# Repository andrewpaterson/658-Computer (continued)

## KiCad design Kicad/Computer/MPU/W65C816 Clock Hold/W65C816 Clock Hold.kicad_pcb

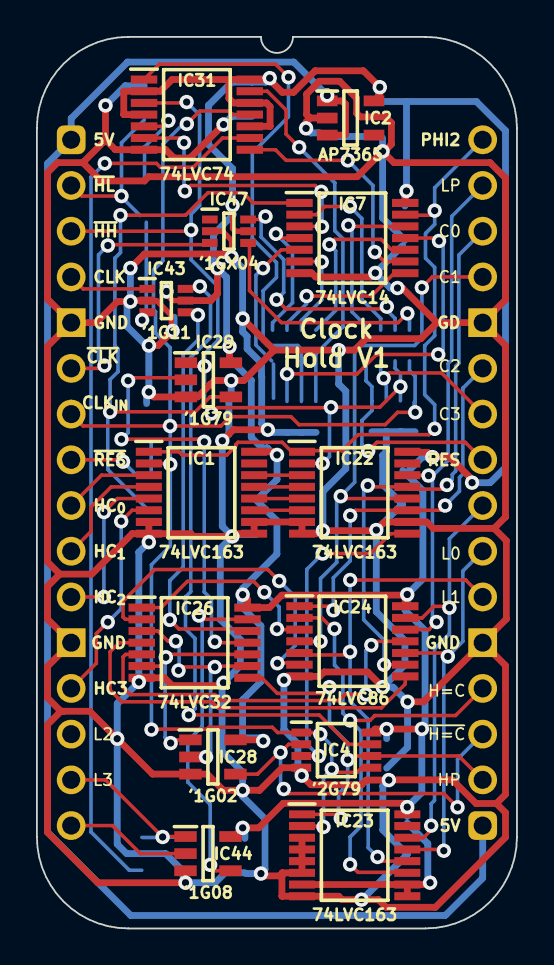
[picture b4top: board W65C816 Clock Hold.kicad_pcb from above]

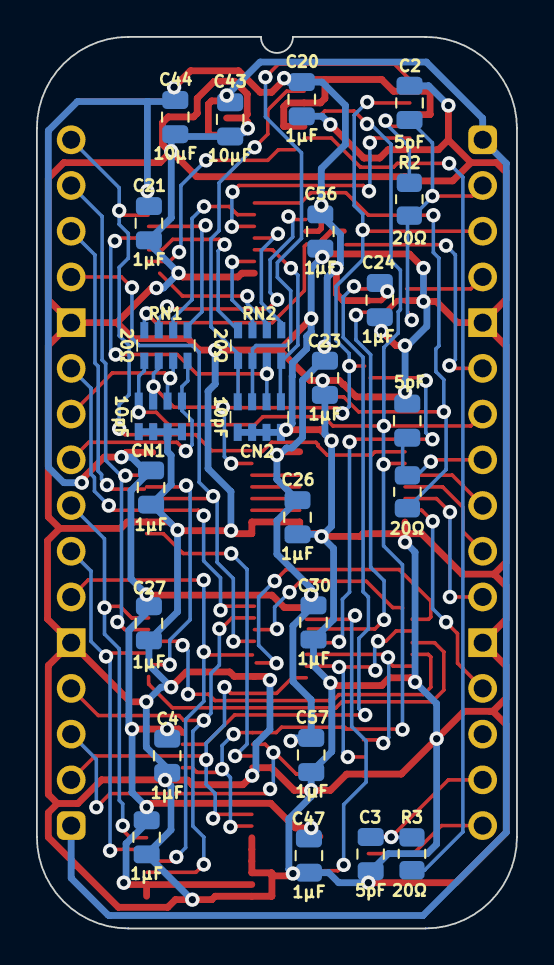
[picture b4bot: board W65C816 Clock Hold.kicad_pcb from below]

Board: 2 copper layers, 26.7 x 49.5 mm, 42 parts (27 on the bottom side), 60 nets.

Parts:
C1, C2, C3: 5pF; C_0805
C4, C20, C21, C23, C24, C25, C26, C27, C28, C30, C47, C56, C57: 1μF; C_0805
C43, C44: 10μF; C_0805
CN1, CN2: CA0612KRX7R9BB100
IC1, IC22, IC23: 74LVC163PW,118; SOP65P640X110-16N
IC2: AP7365-33WG-7; SOT95P285X130-5N
IC4: SN74LVC2G79DCTR; SOP65P400X130-8N
IC7: SN74LVC14APWRG4; SOP65P640X110-14N
IC24: SN74LVC86APWR; SOP65P640X120-14N
IC26: 74LVC32APW,118; SOP65P640X110-14N
IC28: 74LVC1G02GV,125; SOT95P275X110-5N
IC29: 74LVC1G79GV,125; SOT95P275X110-5N
IC31: 74LVC74APW,118; SOP65P640X110-14N
IC43: 74LVC1G11GW-Q100H; SOP65P210X110-6N
IC44: 74LVC1G08GV,125; SOT95P275X110-5N
IC47: 74LVC1GX04GW,125; SOP65P210X110-6N
J1: Conn_02x16_Counter_Clockwise; DIP-32_Board_W22.86mm
J2, J3: Pin_Header_01x16; PinHeader_1x16_P2.54mm_Vertical
R1, R2, R3: 20Ω; R_0805
RN1, RN2: CAY16-200J4LF; CAY16-F4

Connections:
5V: C43.1, IC2.1 (6VIn), IC2.3 (EN), J1.1, J1.17
/3.3V: C4.2, C20.1, C21.1, C23.1, C24.1, C25.1, C26.1, C27.1, C28.1, C30.1, C44.1, C47.1, C56.1, C57.1, IC1.16 (3V), IC2.5 (3.3VOut), IC4.8 (3V), IC7.14 (3V), IC22.16 (3V), IC23.7 (CEP), IC23.9 (~PE), IC23.10 (CET), IC23.16 (3V), IC24.14 (3V), IC26.14 (3V), IC28.5 (3V), IC29.5 (3V), IC31.2 (1D), IC31.4 (~1SD), IC31.10 (~2SD), IC31.12 (2D), IC31.14 (3V), IC43.5 (3V), IC44.5 (3V), IC47.5 (3V)
/CLK H.P.: IC7.4 (2Y), RN2.1 (R1)
/CLK H.P._{s}: CN2.1, IC7.5 (3A), RN2.8 (R1)
/CLK High Pulse_{f}: IC31.5 (1Q), R2.2
/CLK L.P.: IC7.8 (4Y), RN2.2 (R2)
/CLK L.P._{s}: CN2.2, IC7.11 (5A), RN2.7 (R2)
/CLK Low Pulse_{f}: IC31.9 (2Q), R3.2
/HC=CC _{CLK}: IC4.7 (1Q), IC43.6 (C)
/High Pulse+Low Pulse: IC26.11 (4Y), IC29.2 (CP)
/Hold Count_{0}: IC1.14 (Q0), IC22.3 (D0)
/Hold Count_{1}: IC1.13 (Q1), IC22.4 (D1)
/Hold Count_{2}: IC1.12 (Q2), IC22.5 (D2)
/Hold Count_{3}: IC1.11 (Q3), IC22.6 (D3)
/PHI2_{f}: IC7.1 (1A), IC29.4 (Q), R1.2
/~CLK High Pulse: IC7.3 (2A), IC31.6 (~1Q)
/~CLK High Reset Pulse: IC7.6 (3Y), RN2.3 (R3)
/~CLK High Reset Pulse_{s}: CN2.3, IC31.1 (~1RD), RN2.6 (R3)
/~CLK Low Pulse: IC7.9 (4A), IC31.8 (~2Q)
/~CLK Low Reset Pulse: IC7.10 (5Y), RN2.4 (R4)
/~CLK Low Reset Pulse_{s}: CN2.4, IC31.13 (~2RD), RN2.5 (R4)
/~HC=CC _{CLK}: IC4.3 (2Q), IC22.9 (~PE)
/~HC_{0=CC_{0}}: IC24.11 (4Y), IC26.5 (2B)
/~HC_{1=CC_{1}}: IC24.8 (3Y), IC26.4 (2A)
/~HC_{2=CC_{2}}: IC24.6 (2Y), IC26.2 (1B)
/~HC_{3=CC_{3}}: IC24.3 (1Y), IC26.1 (1A)
/~HC_{H=CC_{H}}: IC26.3 (1Y), IC26.9 (3A), IC28.2 (A)
/~HC_{L=CC_{L}}: IC26.6 (2Y), IC26.10 (3B), IC28.1 (B)
/~Hold High·CLK High Pulse·HC=CC: IC26.12 (4A), IC43.4 (Y)
/~Hold Low·CLK Low Pulse: IC26.13 (4B), IC44.4 (Y)
CLK: CN1.3, IC22.2 (CP), IC29.1 (D), IC31.3 (1CP), J1.3, RN1.6 (R3)
CLK High Pulse: C2.1, IC43.3 (B), J1.2, R2.1
CLK Low Pulse: C3.1, IC44.1 (B), J1.15, R3.1
CLK_{IN}: IC47.3 (X1), J1.6
Clk Count_{0}: IC23.14 (Q0), IC24.13 (4B), J1.24
Clk Count_{1}: IC23.13 (Q1), IC24.10 (3B), J1.23
Clk Count_{2}: IC23.12 (Q2), IC24.5 (2B), J1.22
Clk Count_{3}: IC23.11 (Q3), IC24.2 (1B), J1.20
GND: C1.2, C2.2, C3.2, C4.1, C20.2, C21.2, C23.2, C24.2, C25.2, C26.2, C27.2, C28.2, C30.2, C43.2, C44.2, C47.2, C56.2, C57.2, CN1.5, CN1.6, CN1.7, CN1.8, CN2.5, CN2.6, CN2.7, CN2.8, IC1.7 (CEP), IC1.8 (GND), IC1.9 (~PE), IC1.10 (CET), IC2.2 (GND), IC4.4 (GND), IC7.7 (GND), IC22.7 (CEP), IC22.8 (GND), IC22.10 (CET), IC23.3 (D0), IC23.4 (D1), IC23.5 (D2), IC23.6 (D3), IC23.8 (GND), IC24.7 (GND), IC26.7 (GND), IC28.3 (GND), IC29.3 (GND), IC31.7 (GND), IC43.2 (GND), IC44.3 (GND), IC47.2 (GND), J1.5, J1.12, J1.21, J1.28
HC Latch_{0}: IC22.14 (Q0), IC24.12 (4A), J1.31
HC Latch_{1}: IC22.13 (Q1), IC24.9 (3A), J1.30
HC Latch_{2}: IC22.12 (Q2), IC24.4 (2A), J1.29
HC Latch_{3}: IC22.11 (Q3), IC24.1 (1A), J1.27
HC=CC _{~CLK}: IC4.2 (1D), IC28.4 (Y), J1.19
Hold Count_{0}D: IC1.3 (D0), J1.9
Hold Count_{1}D: IC1.4 (D1), J1.10
Hold Count_{2}D: IC1.5 (D2), J1.11
Hold Count_{3}D: IC1.6 (D3), J1.13
unnamed: IC7.2 (1Y), RN1.2 (R2)
unnamed: IC7.12 (6Y), RN1.1 (R1)
unnamed: IC47.6 (Y), RN1.3 (R3)
unnamed: IC47.4 (~Y), RN1.4 (R4)
PHI2: C1.1, J1.8, R1.1
Reset: CN1.1, J1.25, RN1.8 (R1)
~CLK: CN1.4, IC1.2 (CP), IC4.1 (1CP), IC4.5 (2CP), IC23.2 (CP), IC31.11 (2CP), J1.7, RN1.5 (R4)
~HC=CC _{~CLK}: IC4.6 (2D), IC23.1 (~MR), IC26.8 (3Y), J1.18
~Hold High: IC43.1 (A), J1.4
~Hold Low: IC44.2 (A), J1.16
~PHI2: CN1.2, J1.26, RN1.7 (R2)
~Reset: IC1.1 (~MR), IC7.13 (6A), IC22.1 (~MR), J1.32

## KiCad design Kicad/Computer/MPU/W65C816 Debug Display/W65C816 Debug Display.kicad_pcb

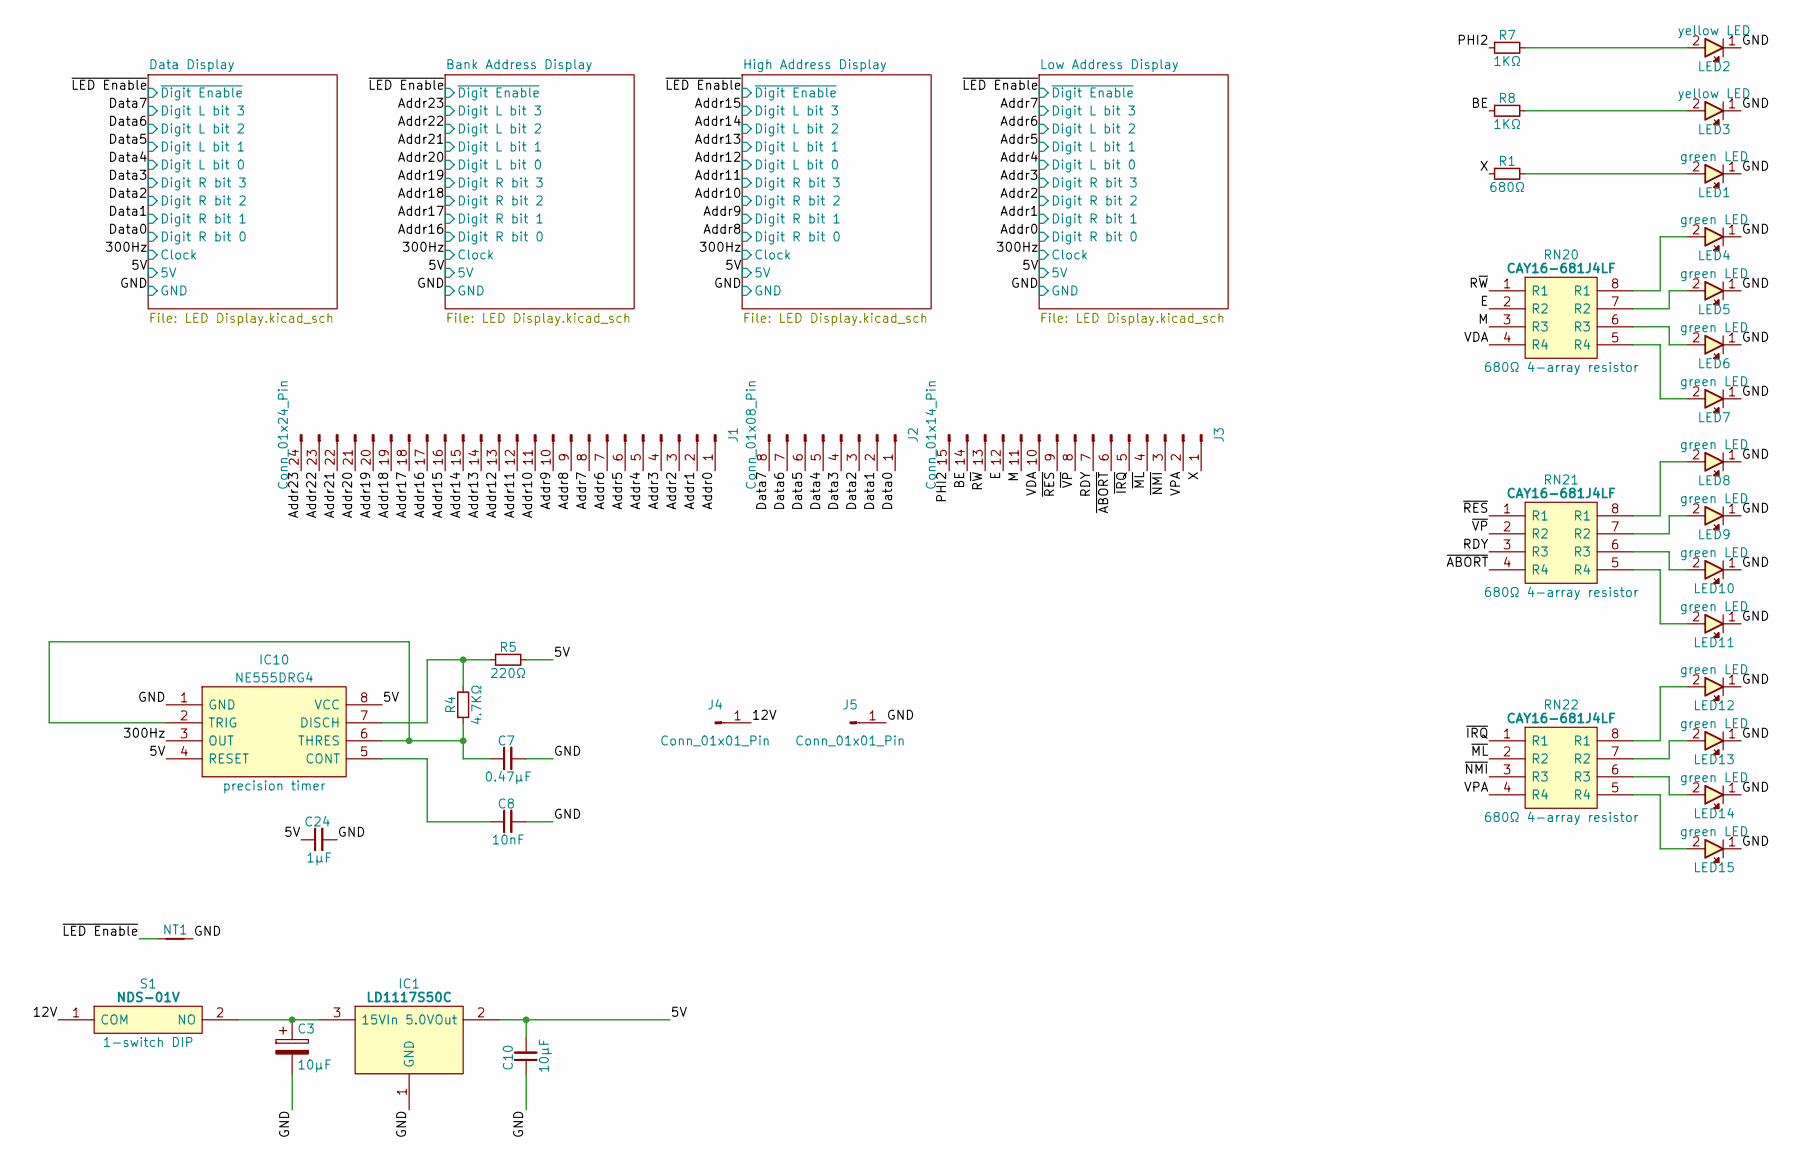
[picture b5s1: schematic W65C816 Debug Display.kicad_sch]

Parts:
C3: 10μF; CP_Radial_D4.0mm_P2.00mm
C7: 0.47μF; C_0805
C8: 10nF; C_0805
C10: 10µF; C_0805
C24: 1µF; C_0805
IC1: LD1117S50C; LD1117S33C; Manufacturer_Part_Number LD1117S50C
IC10: NE555DRG4; SOIC127P600X175-8N; Mouser Part Number 595-NE555DRG4
J1: Conn_01x24_Pin; PinHeader_1x24_P2.54mm_Vertical
J2: Conn_01x08_Pin; PinHeader_1x08_P2.54mm_Vertical
J3: Conn_01x14_Pin; PinHeader_1x15_P2.54mm_Vertical
J4, J5: Conn_01x01_Pin; PinHeader_1x01_P2.54mm_Vertical
LED1, LED4, LED5, LED6, LED7, LED8, LED9, LED10, LED11, LED12, LED13, LED14, LED15: 150224VS73100A; Manufacturer_Part_Number 150224VS73100A; Mouser Part Number 710-150224VS73100A
LED2, LED3: 150224YS73100A; 150224BS73100A
NT1: NetTie; NetTie-2_SMD_Pad0.5mm
R1: 680Ω; R_0805
R4: 4.7KΩ; R_0805
R5: 220Ω; R_0805
R7, R8: 1KΩ; R_0805
RN20, RN21, RN22: CAY16-681J4LF; CAY16-J4; Manufacturer_Part_Number CAY16-681J4LF; Mouser Part Number 652-CAY16-681J4LF
S1: NDS-01V; NDS01V; Mouser Part Number 113-NDS01V

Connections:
/5V: C24.1, IC1.2 (5.0VOut), IC10.4 (RESET), IC10.8 (VCC), R5.2; also elsewhere on the board
/12V: J4.1, S1.1 (COM)
/300Hz: IC10.3 (OUT); also elsewhere on the board
/Addr0: J1.1; also elsewhere on the board
/Addr1: J1.2; also elsewhere on the board
/Addr2: J1.3; also elsewhere on the board
/Addr3: J1.4; also elsewhere on the board
/Addr4: J1.5; also elsewhere on the board
/Addr5: J1.6; also elsewhere on the board
/Addr6: J1.7; also elsewhere on the board
/Addr7: J1.8; also elsewhere on the board
/Addr8: J1.9; also elsewhere on the board
/Addr9: J1.10; also elsewhere on the board
/Addr10: J1.11; also elsewhere on the board
/Addr11: J1.12; also elsewhere on the board
/Addr12: J1.13; also elsewhere on the board
/Addr13: J1.14; also elsewhere on the board
/Addr14: J1.15; also elsewhere on the board
/Addr15: J1.16; also elsewhere on the board
/Addr16: J1.17; also elsewhere on the board
/Addr17: J1.18; also elsewhere on the board
/Addr18: J1.19; also elsewhere on the board
/Addr19: J1.20; also elsewhere on the board
/Addr20: J1.21; also elsewhere on the board
/Addr21: J1.22; also elsewhere on the board
/Addr22: J1.23; also elsewhere on the board
/Addr23: J1.24; also elsewhere on the board
/BE: J3.14, R8.1
/Data0: J2.1; also elsewhere on the board
/Data1: J2.2; also elsewhere on the board
/Data2: J2.3; also elsewhere on the board
/Data3: J2.4; also elsewhere on the board
/Data4: J2.5; also elsewhere on the board
/Data5: J2.6; also elsewhere on the board
/Data6: J2.7; also elsewhere on the board
/Data7: J2.8; also elsewhere on the board
/E: J3.12, RN20.2 (R2)
/GND: C3.2, C7.2, C8.2, C24.2, IC1.1 (GND), IC10.1 (GND), J5.1, LED1.1, LED2.1, LED3.1, LED4.1, LED5.1, LED6.1, LED7.1, LED8.1, LED9.1, LED10.1, LED11.1, LED12.1, LED13.1, LED14.1, LED15.1, NT1.2; also elsewhere on the board
/M: J3.11, RN20.3 (R3)
/PHI2: J3.15, R7.1
/RDY: J3.7, RN21.3 (R3)
/R~W: J3.13, RN20.1 (R1)
/VDA: J3.10, RN20.4 (R4)
/VPA: J3.2, RN22.4 (R4)
/X: J3.1, R1.1
/~ABORT: J3.6, RN21.4 (R4)
/~IRQ: J3.5, RN22.1 (R1)
/~LED Enable: NT1.1; also elsewhere on the board
/~ML: J3.4, RN22.2 (R2)
/~NMI: J3.3, RN22.3 (R3)
/~RES: J3.9, RN21.1 (R1)
/~VP: J3.8, RN21.2 (R2)
unnamed: C3.1, IC1.3 (15VIn), S1.2 (NO)
unnamed: C8.1, IC10.5 (CONT)
unnamed: IC10.7 (DISCH), R4.2, R5.1
unnamed: C7.1, IC10.2 (TRIG), IC10.6 (THRES), R4.1
unnamed: LED1.2, R1.2
unnamed: LED2.2, R7.2
unnamed: LED3.2, R8.2
unnamed: LED4.2, RN20.8 (R1)
unnamed: LED5.2, RN20.7 (R2)
unnamed: LED6.2, RN20.6 (R3)
unnamed: LED7.2, RN20.5 (R4)
unnamed: LED8.2, RN21.8 (R1)
unnamed: LED9.2, RN21.7 (R2)
unnamed: LED10.2, RN21.6 (R3)
unnamed: LED11.2, RN21.5 (R4)
unnamed: LED12.2, RN22.8 (R1)
unnamed: LED13.2, RN22.7 (R2)
unnamed: LED14.2, RN22.6 (R3)
unnamed: LED15.2, RN22.5 (R4)

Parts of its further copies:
C2: 10µF; C_0805

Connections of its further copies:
/5V: C2.2; also elsewhere on the board
/GND: C2.1; also elsewhere on the board

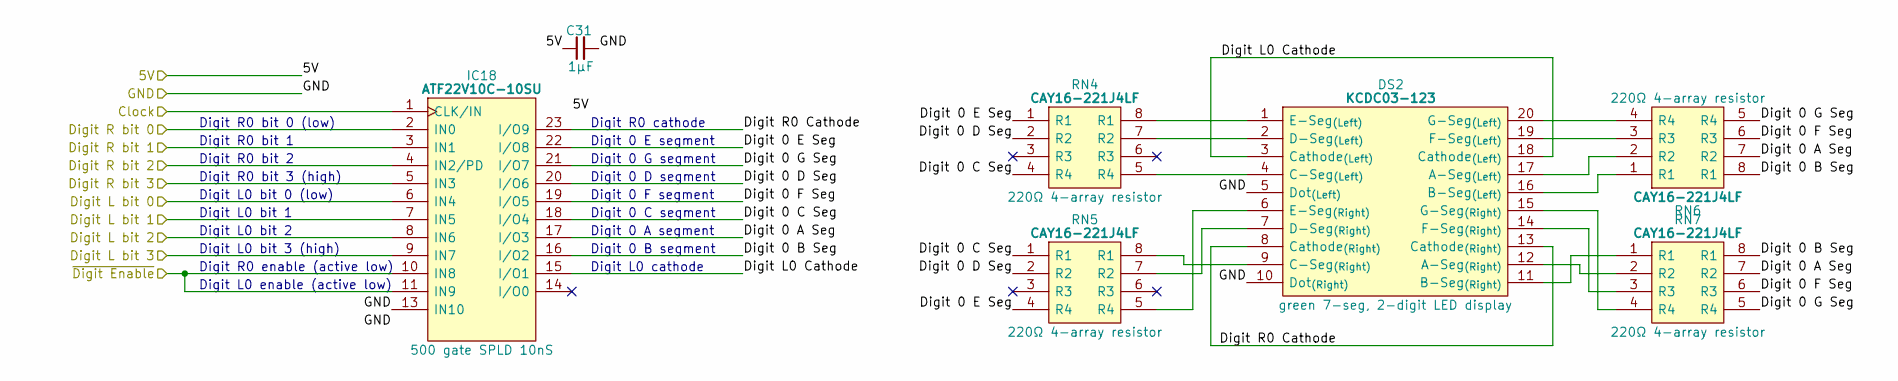
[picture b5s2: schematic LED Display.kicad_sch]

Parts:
C31: 1μF; C_0805
DS2: KCDC03-123; KCDC03123; Manufacturer_Part_Number KCDC03-123; Mouser Part Number N/A
IC18: ATF22V10C-10SU; SOIC127P1032X265-24N; Manufacturer_Part_Number ATF22V10C-10SU; Mouser Part Number 556-ATF22V10C-10SU
RN4, RN5, RN6, RN7: CAY16-221J4LF; CAY16-F4; Manufacturer_Part_Number CAY16-221J4LF; Mouser Part Number 652-CAY16-221J4LF

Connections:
/5V: C31.1, IC18.24 (5V); also elsewhere on the board
/300Hz: IC18.1 (CLK/IN); also elsewhere on the board
/Data0: IC18.2 (IN0); also elsewhere on the board
/Data1: IC18.3 (IN1); also elsewhere on the board
/Data2: IC18.4 (IN2/PD); also elsewhere on the board
/Data3: IC18.5 (IN3); also elsewhere on the board
/Data4: IC18.6 (IN4); also elsewhere on the board
/Data5: IC18.7 (IN5); also elsewhere on the board
/Data6: IC18.8 (IN6); also elsewhere on the board
/Data7: IC18.9 (IN7); also elsewhere on the board
/Data Display/Digit 0 A Seg: IC18.17 (I/O3), RN6.7 (R2), RN7.7 (R2)
/Data Display/Digit 0 B Seg: IC18.16 (I/O2), RN6.8 (R1), RN7.8 (R1)
/Data Display/Digit 0 C Seg: IC18.18 (I/O4), RN4.4 (R4), RN5.1 (R1)
/Data Display/Digit 0 D Seg: IC18.20 (I/O6), RN4.2 (R2), RN5.2 (R2)
/Data Display/Digit 0 E Seg: IC18.22 (I/O8), RN4.1 (R1), RN5.4 (R4)
/Data Display/Digit 0 F Seg: IC18.19 (I/O5), RN6.6 (R3), RN7.6 (R3)
/Data Display/Digit 0 G Seg: IC18.21 (I/O7), RN6.5 (R4), RN7.5 (R4)
/Data Display/Digit L0 Cathode: DS2.3 (Cathode_{(Left)}), DS2.18 (Cathode_{(Left)}), IC18.15 (I/O1)
/Data Display/Digit R0 Cathode: DS2.8 (Cathode_{(Right)}), DS2.13 (Cathode_{(Right)}), IC18.23 (I/O9)
/GND: C31.2, DS2.5 (Dot_{(Left)}), DS2.10 (Dot_{(Right)}), IC18.12 (GND), IC18.13 (IN10); also elsewhere on the board
/~LED Enable: IC18.10 (IN8), IC18.11 (IN9); also elsewhere on the board
unnamed: DS2.17 (A-Seg_{(Left)}), RN6.2 (R2)
unnamed: DS2.12 (A-Seg_{(Right)}), RN7.2 (R2)
unnamed: DS2.16 (B-Seg_{(Left)}), RN6.1 (R1)
unnamed: DS2.11 (B-Seg_{(Right)}), RN7.1 (R1)
unnamed: DS2.4 (C-Seg_{(Left)}), RN4.5 (R4)
unnamed: DS2.9 (C-Seg_{(Right)}), RN5.8 (R1)
unnamed: DS2.2 (D-Seg_{(Left)}), RN4.7 (R2)
unnamed: DS2.7 (D-Seg_{(Right)}), RN5.7 (R2)
unnamed: DS2.1 (E-Seg_{(Left)}), RN4.8 (R1)
unnamed: DS2.6 (E-Seg_{(Right)}), RN5.5 (R4)
unnamed: DS2.19 (F-Seg_{(Left)}), RN6.3 (R3)
unnamed: DS2.14 (F-Seg_{(Right)}), RN7.3 (R3)
unnamed: DS2.20 (G-Seg_{(Left)}), RN6.4 (R4)
unnamed: DS2.15 (G-Seg_{(Right)}), RN7.4 (R4)

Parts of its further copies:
C33, C35, C37: 1μF; C_0805
DS3, DS4, DS5: KCDC03-123; KCDC03123; Manufacturer_Part_Number KCDC03-123; Mouser Part Number N/A
IC19, IC20, IC21: ATF22V10C-10SU; SOIC127P1032X265-24N; Manufacturer_Part_Number ATF22V10C-10SU; Mouser Part Number 556-ATF22V10C-10SU
RN8, RN9, RN10, RN11, RN12, RN13, RN14, RN15, RN16, RN17, RN18, RN19: CAY16-221J4LF; CAY16-F4; Manufacturer_Part_Number CAY16-221J4LF; Mouser Part Number 652-CAY16-221J4LF

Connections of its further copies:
/5V: C33.1, C35.1, C37.1, IC19.24 (5V), IC20.24 (5V), IC21.24 (5V); also elsewhere on the board
/300Hz: IC19.1 (CLK/IN), IC20.1 (CLK/IN), IC21.1 (CLK/IN); also elsewhere on the board
/Addr0: IC20.2 (IN0); also elsewhere on the board
/Addr1: IC20.3 (IN1); also elsewhere on the board
/Addr2: IC20.4 (IN2/PD); also elsewhere on the board
/Addr3: IC20.5 (IN3); also elsewhere on the board
/Addr4: IC20.6 (IN4); also elsewhere on the board
/Addr5: IC20.7 (IN5); also elsewhere on the board
/Addr6: IC20.8 (IN6); also elsewhere on the board
/Addr7: IC20.9 (IN7); also elsewhere on the board
/Addr8: IC19.2 (IN0); also elsewhere on the board
/Addr9: IC19.3 (IN1); also elsewhere on the board
/Addr10: IC19.4 (IN2/PD); also elsewhere on the board
/Addr11: IC19.5 (IN3); also elsewhere on the board
/Addr12: IC19.6 (IN4); also elsewhere on the board
/Addr13: IC19.7 (IN5); also elsewhere on the board
/Addr14: IC19.8 (IN6); also elsewhere on the board
/Addr15: IC19.9 (IN7); also elsewhere on the board
/Addr16: IC21.2 (IN0); also elsewhere on the board
/Addr17: IC21.3 (IN1); also elsewhere on the board
/Addr18: IC21.4 (IN2/PD); also elsewhere on the board
/Addr19: IC21.5 (IN3); also elsewhere on the board
/Addr20: IC21.6 (IN4); also elsewhere on the board
/Addr21: IC21.7 (IN5); also elsewhere on the board
/Addr22: IC21.8 (IN6); also elsewhere on the board
/Addr23: IC21.9 (IN7); also elsewhere on the board
/Bank Address Display/Digit 0 A Seg: IC21.17 (I/O3), RN18.7 (R2), RN19.7 (R2)
/Bank Address Display/Digit 0 B Seg: IC21.16 (I/O2), RN18.8 (R1), RN19.8 (R1)
/Bank Address Display/Digit 0 C Seg: IC21.18 (I/O4), RN16.4 (R4), RN17.1 (R1)
/Bank Address Display/Digit 0 D Seg: IC21.20 (I/O6), RN16.2 (R2), RN17.2 (R2)
/Bank Address Display/Digit 0 E Seg: IC21.22 (I/O8), RN16.1 (R1), RN17.4 (R4)
/Bank Address Display/Digit 0 F Seg: IC21.19 (I/O5), RN18.6 (R3), RN19.6 (R3)
/Bank Address Display/Digit 0 G Seg: IC21.21 (I/O7), RN18.5 (R4), RN19.5 (R4)
/Bank Address Display/Digit L0 Cathode: DS5.3 (Cathode_{(Left)}), DS5.18 (Cathode_{(Left)}), IC21.15 (I/O1)
/Bank Address Display/Digit R0 Cathode: DS5.8 (Cathode_{(Right)}), DS5.13 (Cathode_{(Right)}), IC21.23 (I/O9)
/GND: C33.2, C35.2, C37.2, DS3.5 (Dot_{(Left)}), DS3.10 (Dot_{(Right)}), DS4.5 (Dot_{(Left)}), DS4.10 (Dot_{(Right)}), DS5.5 (Dot_{(Left)}), DS5.10 (Dot_{(Right)}), IC19.12 (GND), IC19.13 (IN10), IC20.12 (GND), IC20.13 (IN10), IC21.12 (GND), IC21.13 (IN10); also elsewhere on the board
/High Address Display/Digit 0 A Seg: IC19.17 (I/O3), RN10.7 (R2), RN11.7 (R2)
/High Address Display/Digit 0 B Seg: IC19.16 (I/O2), RN10.8 (R1), RN11.8 (R1)
/High Address Display/Digit 0 C Seg: IC19.18 (I/O4), RN8.4 (R4), RN9.1 (R1)
/High Address Display/Digit 0 D Seg: IC19.20 (I/O6), RN8.2 (R2), RN9.2 (R2)
/High Address Display/Digit 0 E Seg: IC19.22 (I/O8), RN8.1 (R1), RN9.4 (R4)
/High Address Display/Digit 0 F Seg: IC19.19 (I/O5), RN10.6 (R3), RN11.6 (R3)
/High Address Display/Digit 0 G Seg: IC19.21 (I/O7), RN10.5 (R4), RN11.5 (R4)
/High Address Display/Digit L0 Cathode: DS3.3 (Cathode_{(Left)}), DS3.18 (Cathode_{(Left)}), IC19.15 (I/O1)
/High Address Display/Digit R0 Cathode: DS3.8 (Cathode_{(Right)}), DS3.13 (Cathode_{(Right)}), IC19.23 (I/O9)
/Low Address Display/Digit 0 A Seg: IC20.17 (I/O3), RN14.7 (R2), RN15.7 (R2)
/Low Address Display/Digit 0 B Seg: IC20.16 (I/O2), RN14.8 (R1), RN15.8 (R1)
/Low Address Display/Digit 0 C Seg: IC20.18 (I/O4), RN12.4 (R4), RN13.1 (R1)
/Low Address Display/Digit 0 D Seg: IC20.20 (I/O6), RN12.2 (R2), RN13.2 (R2)
/Low Address Display/Digit 0 E Seg: IC20.22 (I/O8), RN12.1 (R1), RN13.4 (R4)
/Low Address Display/Digit 0 F Seg: IC20.19 (I/O5), RN14.6 (R3), RN15.6 (R3)
/Low Address Display/Digit 0 G Seg: IC20.21 (I/O7), RN14.5 (R4), RN15.5 (R4)
/Low Address Display/Digit L0 Cathode: DS4.3 (Cathode_{(Left)}), DS4.18 (Cathode_{(Left)}), IC20.15 (I/O1)
/Low Address Display/Digit R0 Cathode: DS4.8 (Cathode_{(Right)}), DS4.13 (Cathode_{(Right)}), IC20.23 (I/O9)
/~LED Enable: IC19.10 (IN8), IC19.11 (IN9), IC20.10 (IN8), IC20.11 (IN9), IC21.10 (IN8), IC21.11 (IN9); also elsewhere on the board
unnamed: DS3.17 (A-Seg_{(Left)}), RN10.2 (R2)
unnamed: DS3.12 (A-Seg_{(Right)}), RN11.2 (R2)
unnamed: DS3.16 (B-Seg_{(Left)}), RN10.1 (R1)
unnamed: DS3.11 (B-Seg_{(Right)}), RN11.1 (R1)
unnamed: DS3.4 (C-Seg_{(Left)}), RN8.5 (R4)
unnamed: DS3.9 (C-Seg_{(Right)}), RN9.8 (R1)
unnamed: DS3.2 (D-Seg_{(Left)}), RN8.7 (R2)
unnamed: DS3.7 (D-Seg_{(Right)}), RN9.7 (R2)
unnamed: DS3.1 (E-Seg_{(Left)}), RN8.8 (R1)
unnamed: DS3.6 (E-Seg_{(Right)}), RN9.5 (R4)
unnamed: DS3.19 (F-Seg_{(Left)}), RN10.3 (R3)
unnamed: DS3.14 (F-Seg_{(Right)}), RN11.3 (R3)
unnamed: DS3.20 (G-Seg_{(Left)}), RN10.4 (R4)
unnamed: DS3.15 (G-Seg_{(Right)}), RN11.4 (R4)
unnamed: DS4.17 (A-Seg_{(Left)}), RN14.2 (R2)
unnamed: DS4.12 (A-Seg_{(Right)}), RN15.2 (R2)
unnamed: DS4.16 (B-Seg_{(Left)}), RN14.1 (R1)
unnamed: DS4.11 (B-Seg_{(Right)}), RN15.1 (R1)
unnamed: DS4.4 (C-Seg_{(Left)}), RN12.5 (R4)
unnamed: DS4.9 (C-Seg_{(Right)}), RN13.8 (R1)
unnamed: DS4.2 (D-Seg_{(Left)}), RN12.7 (R2)
unnamed: DS4.7 (D-Seg_{(Right)}), RN13.7 (R2)
unnamed: DS4.1 (E-Seg_{(Left)}), RN12.8 (R1)
unnamed: DS4.6 (E-Seg_{(Right)}), RN13.5 (R4)
unnamed: DS4.19 (F-Seg_{(Left)}), RN14.3 (R3)
unnamed: DS4.14 (F-Seg_{(Right)}), RN15.3 (R3)
unnamed: DS4.20 (G-Seg_{(Left)}), RN14.4 (R4)
unnamed: DS4.15 (G-Seg_{(Right)}), RN15.4 (R4)
unnamed: DS5.17 (A-Seg_{(Left)}), RN18.2 (R2)
unnamed: DS5.12 (A-Seg_{(Right)}), RN19.2 (R2)
unnamed: DS5.16 (B-Seg_{(Left)}), RN18.1 (R1)
unnamed: DS5.11 (B-Seg_{(Right)}), RN19.1 (R1)
unnamed: DS5.4 (C-Seg_{(Left)}), RN16.5 (R4)
unnamed: DS5.9 (C-Seg_{(Right)}), RN17.8 (R1)
unnamed: DS5.2 (D-Seg_{(Left)}), RN16.7 (R2)
unnamed: DS5.7 (D-Seg_{(Right)}), RN17.7 (R2)
unnamed: DS5.1 (E-Seg_{(Left)}), RN16.8 (R1)
unnamed: DS5.6 (E-Seg_{(Right)}), RN17.5 (R4)
unnamed: DS5.19 (F-Seg_{(Left)}), RN18.3 (R3)
unnamed: DS5.14 (F-Seg_{(Right)}), RN19.3 (R3)
unnamed: DS5.20 (G-Seg_{(Left)}), RN18.4 (R4)
unnamed: DS5.15 (G-Seg_{(Right)}), RN19.4 (R4)

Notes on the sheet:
Digit L0 enable (active low)
Digit R0 bit 3 (high)
Digit 0 B segment
Digit 0 F segment
Digit R0 enable (active low)
Digit 0 C segment
Digit L0 cathode
Digit 0 E segment
Digit L0 bit 0 (low)
Digit L0 bit 2
Digit R0 cathode
Digit 0 A segment
Digit R0 bit 0 (low)
Digit 0 D segment
Digit R0 bit 1
Digit 0 G segment
Digit R0 bit 2
Digit L0 bit 3 (high)
Digit L0 bit 1

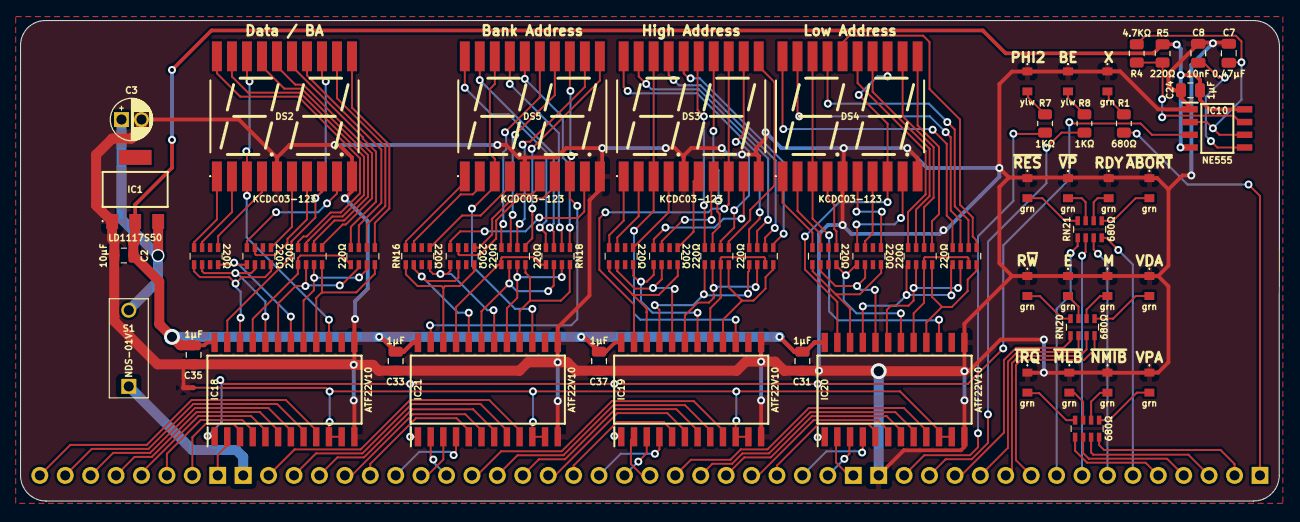
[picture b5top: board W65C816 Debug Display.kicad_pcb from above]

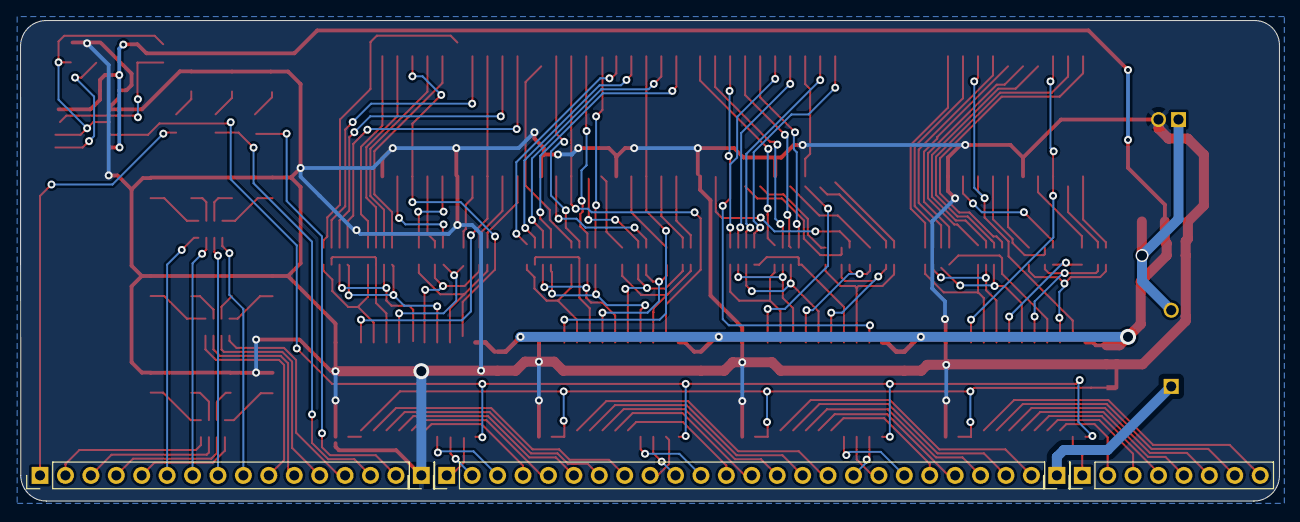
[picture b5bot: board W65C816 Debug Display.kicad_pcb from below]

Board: 2 copper layers, 125.8 x 48.0 mm, 65 parts (5 on the bottom side), 163 nets.

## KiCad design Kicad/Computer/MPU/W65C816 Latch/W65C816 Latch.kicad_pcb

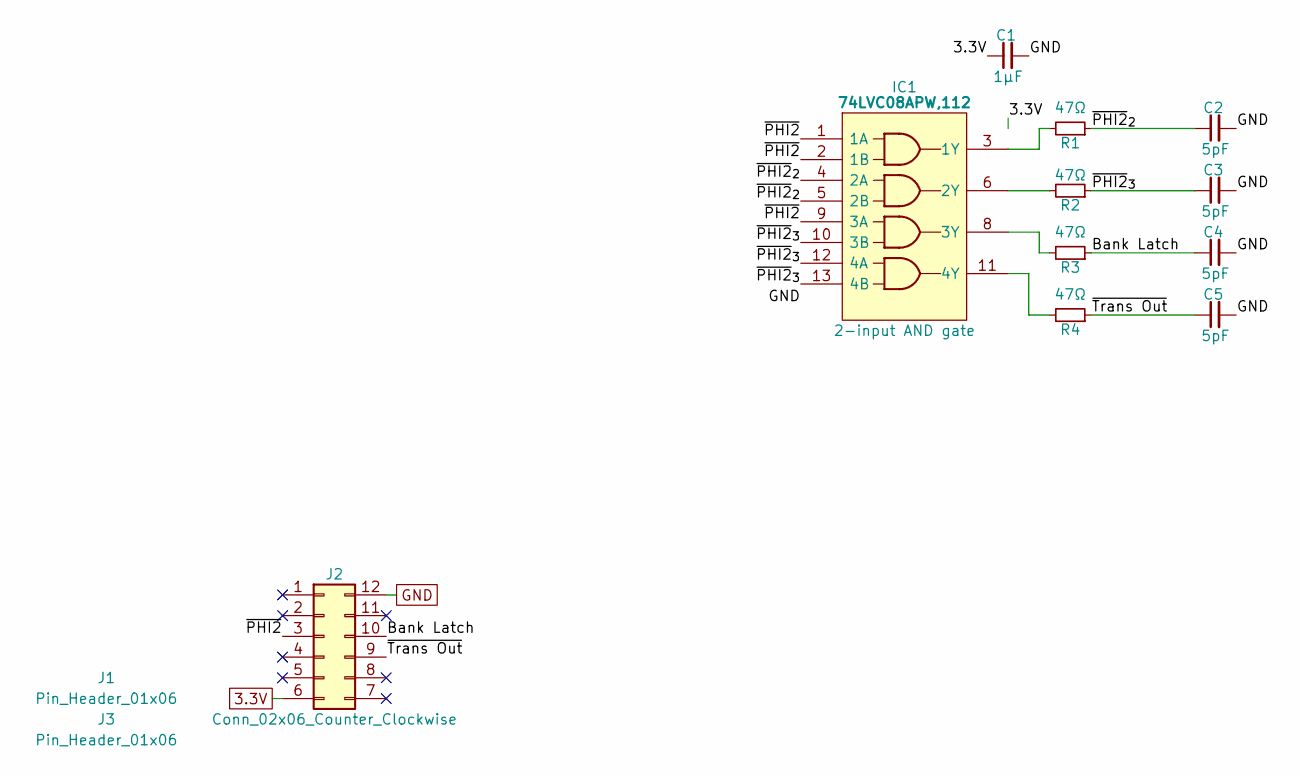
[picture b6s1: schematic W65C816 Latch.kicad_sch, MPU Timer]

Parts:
C1: 1μF; C_0805
C2, C3, C4, C5: 5pF; C_0805
IC1: 74LVC08APW,112; SOP65P640X110-14N; Mouser Part Number 771-74LVC08APW
J1, J3: Pin_Header_01x06; PinHeader_1x06_P2.54mm_Vertical
J2: Conn_02x06_Counter_Clockwise; DIP-12_Board_W22.86mm_Alt
R1, R2, R3, R4: 47Ω; R_0805

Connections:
3.3V: C1.1, IC1.14 (3V), J2.6
/Bank Latch: C4.1, J2.10, R3.1
/~PHI2: IC1.1 (1A), IC1.2 (1B), IC1.9 (3A), J2.3
/~PHI2_{2}: C2.1, IC1.4 (2A), IC1.5 (2B), R1.1
/~PHI2_{3}: C3.1, IC1.10 (3B), IC1.12 (4A), IC1.13 (4B), R2.1
/~Trans Out: C5.1, J2.9, R4.1
GND: C1.2, C2.2, C3.2, C4.2, C5.2, IC1.7 (GND), J2.12
unnamed: IC1.3 (1Y), R1.2
unnamed: IC1.6 (2Y), R2.2
unnamed: IC1.8 (3Y), R3.2
unnamed: IC1.11 (4Y), R4.2

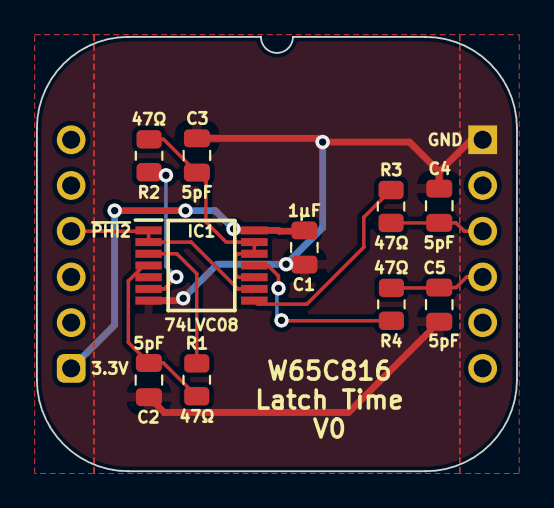
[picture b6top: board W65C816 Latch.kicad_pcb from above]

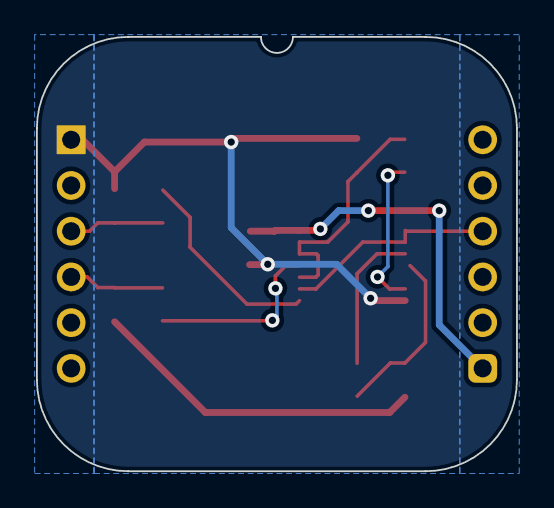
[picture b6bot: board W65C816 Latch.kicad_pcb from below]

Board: 2 copper layers, 26.7 x 24.1 mm, 13 parts (2 on the bottom side), 11 nets.

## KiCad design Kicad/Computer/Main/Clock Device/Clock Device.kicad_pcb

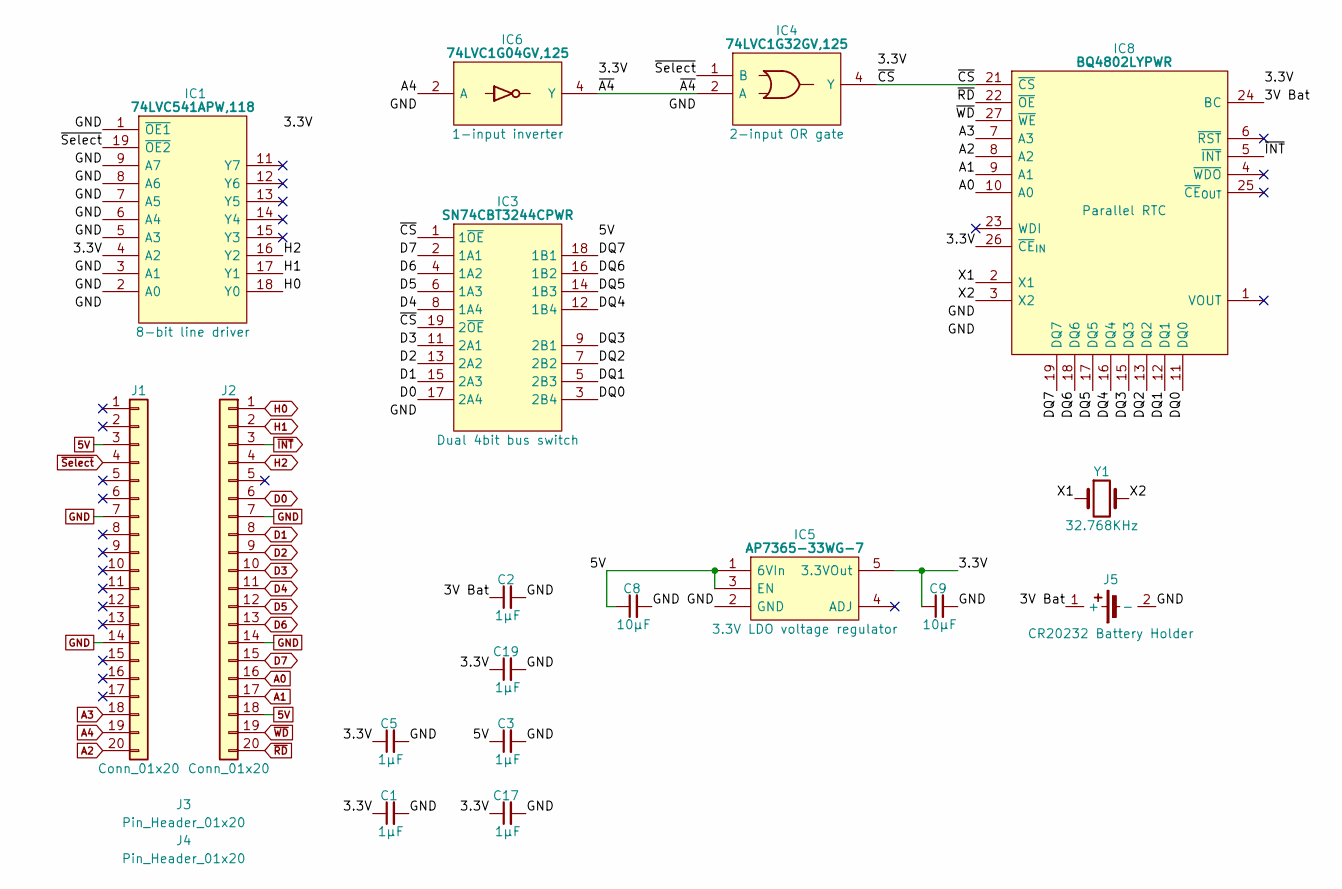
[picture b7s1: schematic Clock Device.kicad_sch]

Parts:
C1, C2, C3, C5, C17, C19: 1μF; C_0805
C8, C9: 10µF; C_0805
IC1: 74LVC541APW,118; SOP65P640X110-20N; Mouser Part Number 771-74LVC541APW-T
IC3: SN74CBT3244CPWR; SOP65P640X120-20N; Manufacturer_Part_Number SN74CBT3244CPWR; Mouser Part Number 595-SN74CBT3244CPWR
IC4: 74LVC1G32GV,125; SOT95P275X110-5N; Manufacturer_Part_Number 74LVC1G32GV,125; Mouser Part Number 771-LVC1G32GV125
IC5: AP7365-33WG-7; SOT95P285X130-5N; Manufacturer_Part_Number AP7365-33WG-7; Mouser Part Number 621-AP7365-33WG-7
IC6: 74LVC1G04GV,125; SOT95P275X110-5N; Manufacturer_Part_Number 74LVC1G04GV,125; Mouser Part Number 771-74LVC1G04GV
IC8: BQ4802LYPWR; SOP65P640X120-28N; Manufacturer_Part_Number BQ4802LYPWR
J1, J2: Conn_01x20; SIP_20_Pins
J3, J4: Pin_Header_01x20; PinHeader_1x20_P2.54mm_Vertical
J5: 237-8270
Y1: 32.768KHz; SC32S7PF20PPM

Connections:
5V: C3.1, C8.1, IC3.20 (5V), IC5.1 (6VIn), IC5.3 (EN), J1.3, J2.18
/3.3V: C1.1, C5.1, C9.1, C17.1, C19.1, IC1.4 (A2), IC1.20 (3V), IC4.5 (3V), IC5.5 (3.3VOut), IC6.5 (3V), IC8.26 (~CE_{IN}), IC8.28 (3V)
/3V Bat: C2.1, IC8.24 (BC), J5.1 (+)
/DQ0: IC3.3 (2B4), IC8.11 (DQ0)
/DQ1: IC3.5 (2B3), IC8.12 (DQ1)
/DQ2: IC3.7 (2B2), IC8.13 (DQ2)
/DQ3: IC3.9 (2B1), IC8.15 (DQ3)
/DQ4: IC3.12 (1B4), IC8.16 (DQ4)
/DQ5: IC3.14 (1B3), IC8.17 (DQ5)
/DQ6: IC3.16 (1B2), IC8.18 (DQ6)
/DQ7: IC3.18 (1B1), IC8.19 (DQ7)
/X1: IC8.2 (X1), Y1.1
/X2: IC8.3 (X2), Y1.2
/~A4: IC4.2 (A), IC6.4 (Y)
/~CS: IC3.1 (1~OE), IC3.19 (2~OE), IC4.4 (Y), IC8.21 (~CS)
A0: IC8.10 (A0), J2.16
A1: IC8.9 (A1), J2.17
A2: IC8.8 (A2), J1.20
A3: IC8.7 (A3), J1.18
A4: IC6.2 (A), J1.19
D0: IC3.17 (2A4), J2.6
D1: IC3.15 (2A3), J2.8
D2: IC3.13 (2A2), J2.9
D3: IC3.11 (2A1), J2.10
D4: IC3.8 (1A4), J2.11
D5: IC3.6 (1A3), J2.12
D6: IC3.4 (1A2), J2.13
D7: IC3.2 (1A1), J2.15
GND: C1.2, C2.2, C3.2, C5.2, C8.2, C9.2, C17.2, C19.2, IC1.1 (~OE1), IC1.2 (A0), IC1.3 (A1), IC1.5 (A3), IC1.6 (A4), IC1.7 (A5), IC1.8 (A6), IC1.9 (A7), IC1.10 (GND), IC3.10 (GND), IC4.3 (GND), IC5.2 (GND), IC6.3 (GND), IC8.14 (GND), IC8.20 (GND), J1.7, J1.14, J2.7, J2.14, J5.2 (-)
H0: IC1.18 (Y0), J2.1
H1: IC1.17 (Y1), J2.2
H2: IC1.16 (Y2), J2.4
~INT: IC8.5 (~INT), J2.3
~RD: IC8.22 (~OE), J2.20
~Select: IC1.19 (~OE2), IC4.1 (B), J1.4
~WD: IC8.27 (~WE), J2.19

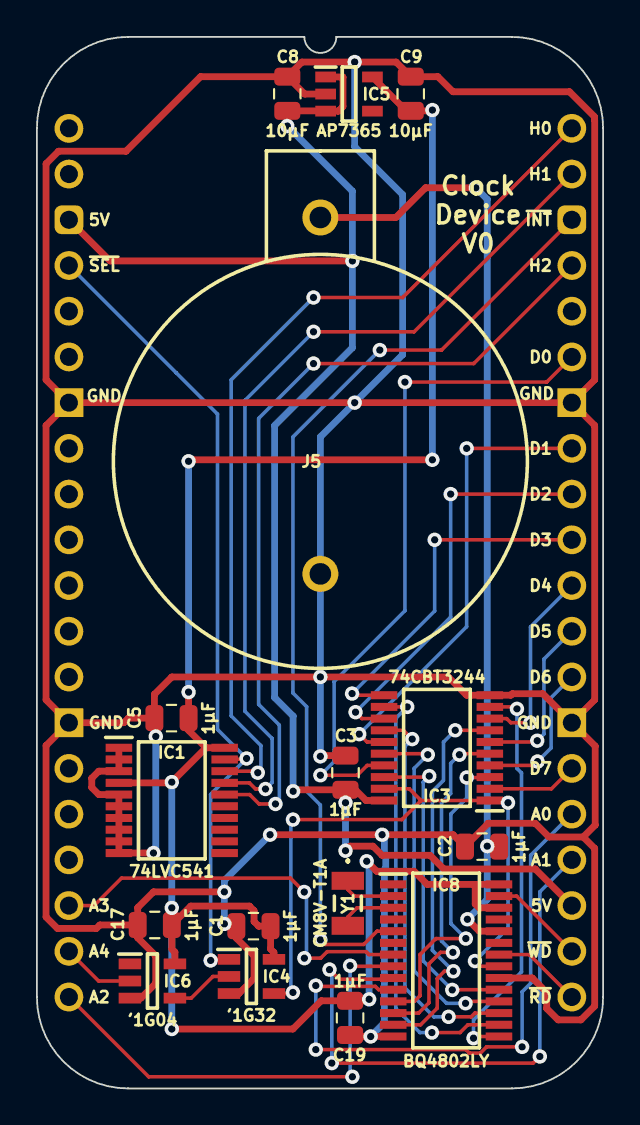
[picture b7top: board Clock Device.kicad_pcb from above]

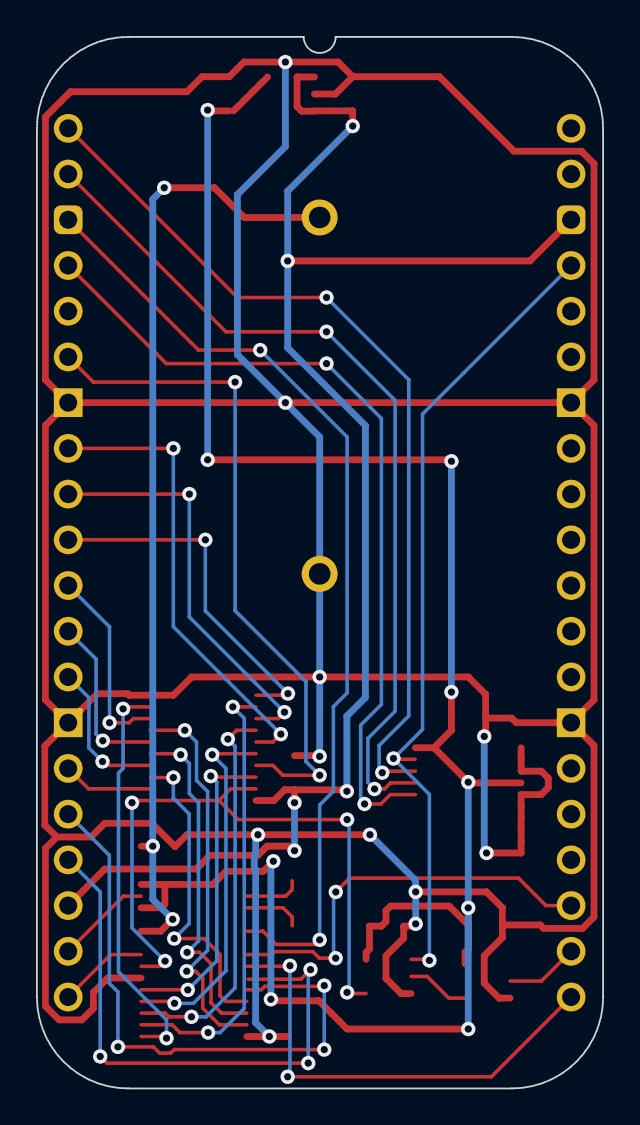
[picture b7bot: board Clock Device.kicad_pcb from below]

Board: 2 copper layers, 31.5 x 58.4 mm, 20 parts (2 on the bottom side), 36 nets.
